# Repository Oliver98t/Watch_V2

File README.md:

# Watch_V2
Firmware, schematics and CAD files for an atmega328p based wristwatch 

Hi there, this watch is supposed to fill a nerdy need of mine and that is to simply display the time in binary format purely for my geek credibility.
The watch will go into a deep sleep after 10 seconds and can be reactivated with the left push button. The date and time is configurable and can also be displayed in decimal format. 

Have a great day!

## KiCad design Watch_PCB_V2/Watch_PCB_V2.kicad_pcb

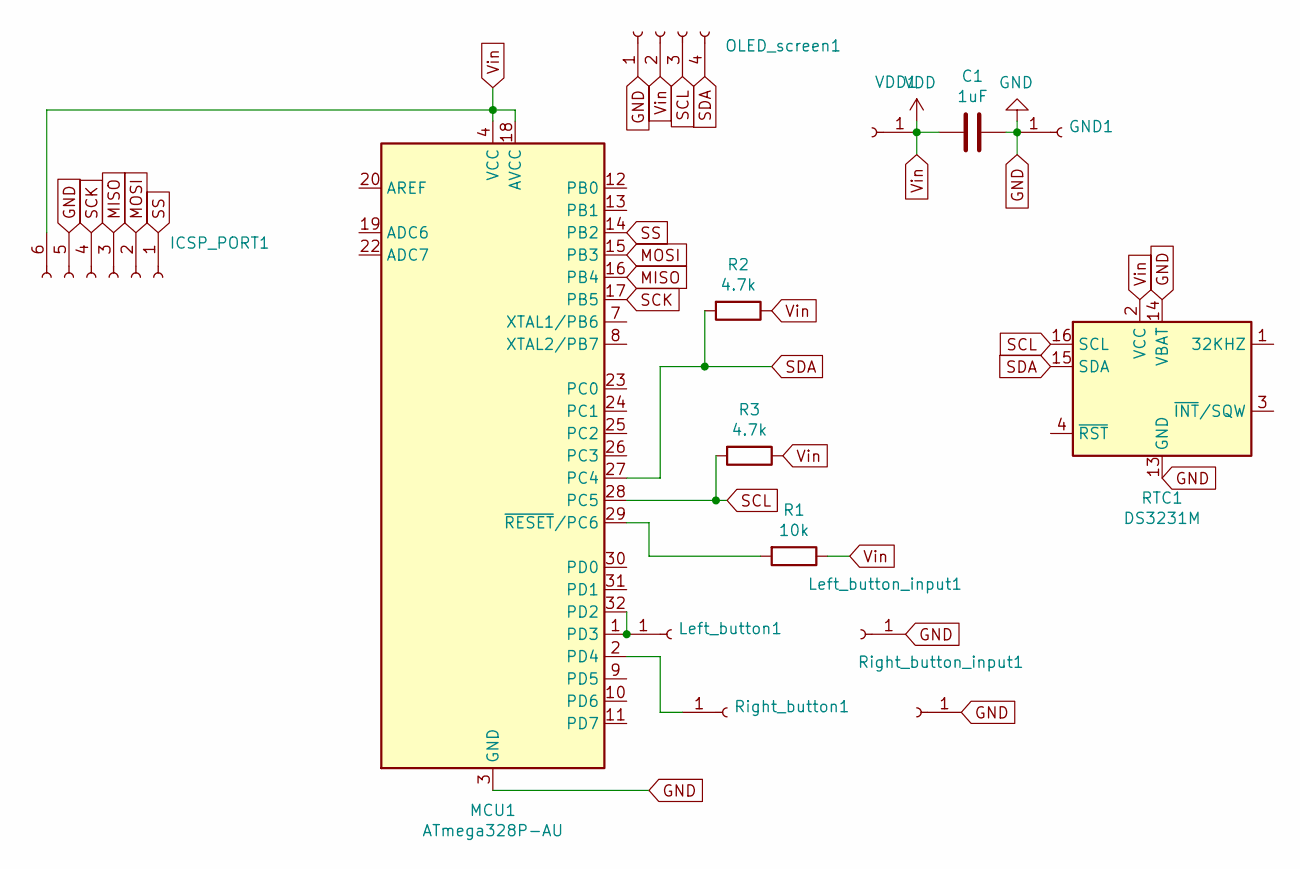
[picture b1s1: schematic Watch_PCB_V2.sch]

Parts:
C1: 1uF; C_1206_3216Metric_Pad1.33x1.80mm_HandSolder
GND1: PinHeader_1x01_P1.00mm_Vertical
ICSP_PORT1: PinHeader_1x06_P2.00mm_Vertical
Left_button1: PinHeader_1x01_P1.00mm_Vertical
Left_button_input1: PinHeader_1x01_P1.00mm_Vertical
MCU1: ATmega328P-AU; TQFP-32_7x7mm_P0.8mm
OLED_screen1: PinHeader_1x04_P2.00mm_Vertical
R1: 10k; R_1206_3216Metric_Pad1.30x1.75mm_HandSolder
R2, R3: 4.7k; R_1206_3216Metric_Pad1.30x1.75mm_HandSolder
RTC1: DS3231M; SOIC-16W_7.5x10.3mm_P1.27mm
Right_button1: PinHeader_1x01_P1.00mm_Vertical
Right_button_input1: PinHeader_1x01_P1.00mm_Vertical
VDD1: PinHeader_1x01_P1.00mm_Vertical

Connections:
GND: C1.2, GND1.1, ICSP_PORT1.5, Left_button_input1.1, MCU1.3 (GND), MCU1.5 (GND), MCU1.21 (GND), OLED_screen1.1, RTC1.5 (GND), RTC1.6 (GND), RTC1.7 (GND), RTC1.8 (GND), RTC1.9 (GND), RTC1.10 (GND), RTC1.11 (GND), RTC1.12 (GND), RTC1.13 (GND), RTC1.14 (VBAT), Right_button_input1.1
MISO: ICSP_PORT1.3, MCU1.16 (PB4)
MOSI: ICSP_PORT1.2, MCU1.15 (PB3)
unnamed: Left_button1.1, MCU1.1 (PD3), MCU1.32 (PD2)
unnamed: MCU1.2 (PD4), Right_button1.1
unnamed: MCU1.29 (~RESET~/PC6), R1.2
SCK: ICSP_PORT1.4, MCU1.17 (PB5)
SCL: MCU1.28 (PC5), OLED_screen1.3, R3.2, RTC1.16 (SCL)
SDA: MCU1.27 (PC4), OLED_screen1.4, R2.2, RTC1.15 (SDA)
SS: ICSP_PORT1.1, MCU1.14 (PB2)
Vin: C1.1, ICSP_PORT1.6, MCU1.4 (VCC), MCU1.6 (VCC), MCU1.18 (AVCC), OLED_screen1.2, R1.1, R2.1, R3.1, RTC1.2 (VCC), VDD1.1

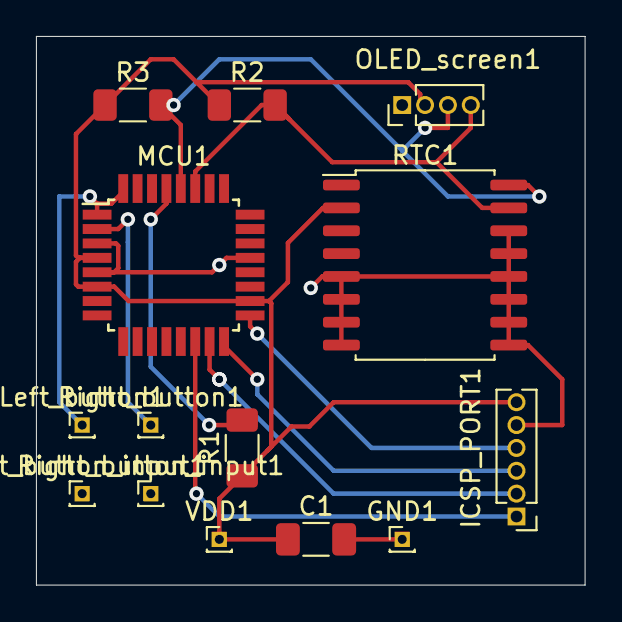
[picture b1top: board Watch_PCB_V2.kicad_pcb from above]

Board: 2 copper layers, 30.5 x 30.5 mm, 14 parts (0 on the bottom side), 11 nets.

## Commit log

2022-02-09 First upload of watch firmware and kicad files
2022-02-23 PCB: deep sleep interrupt now attached left button input
2022-02-23 CAD: added tab to upper case for easy removal
